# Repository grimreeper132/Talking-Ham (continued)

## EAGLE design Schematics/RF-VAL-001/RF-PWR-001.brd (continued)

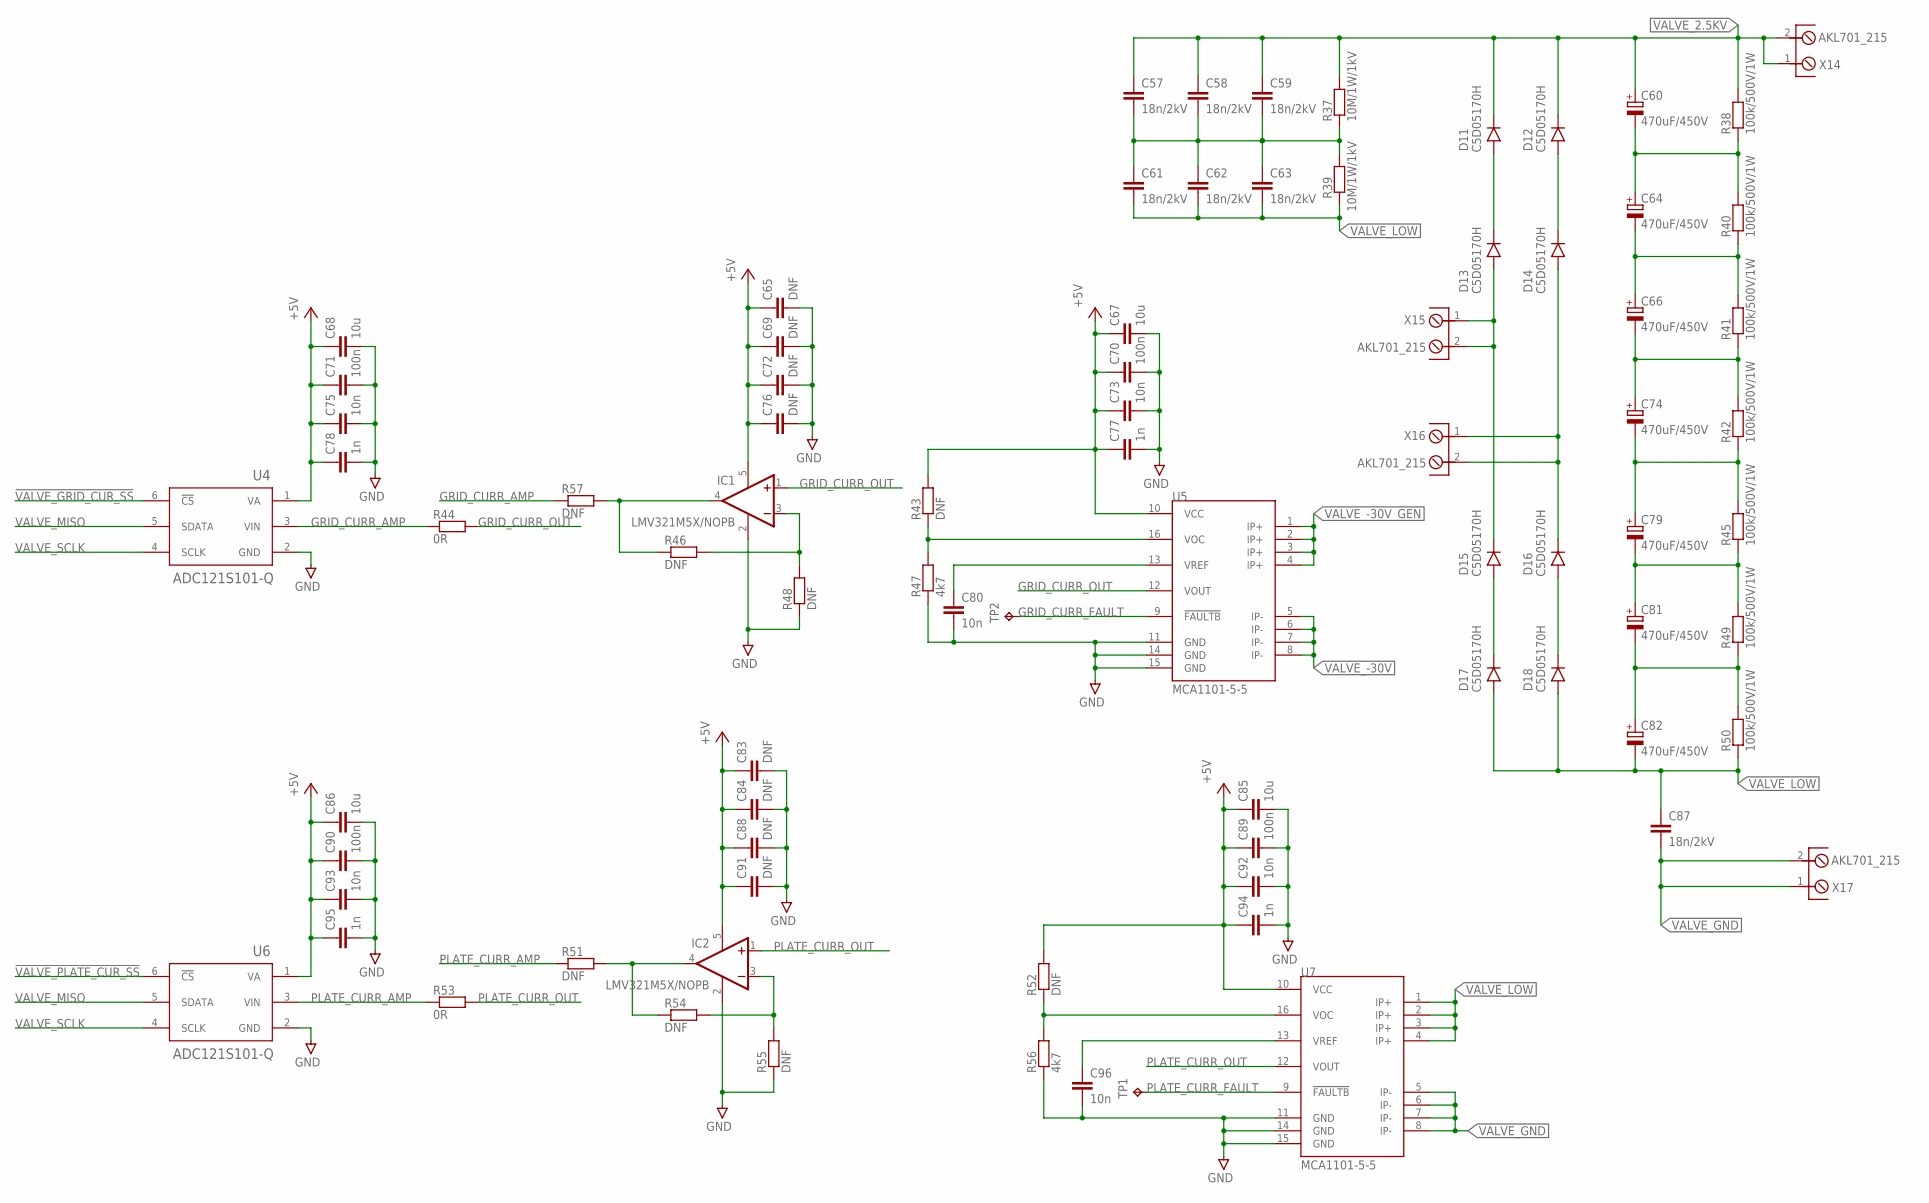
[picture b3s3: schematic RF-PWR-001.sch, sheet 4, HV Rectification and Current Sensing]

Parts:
C57, C58, C59, C61, C62, C63, C87: 18n/2kV; C050-075X075
C60, C64, C66, C74, C79, C81, C82: 470uF/450V; STYLE_D(35MM)
C65, C83: DNF; C0805
C67, C68, C85, C86: 10u; C0805
C69, C72, C76, C84, C88, C91: DNF; C0603
C70, C71, C89, C90: 100n; C0603
C73, C75, C80, C92, C93, C96: 10n; C0603
C77, C78, C94, C95: 1n; C0603
D11, D12, D13, D14, D15, D16, D17, D18: C5D05170H; TO-247-2
IC1, IC2: LMV321M5X/NOPB; SOT23-5
R37, R39: 10M/1W/1kV; R2512
R38, R40, R41, R42, R45, R49, R50: 100k/500V/1W; R2512
R43, R46, R48, R51, R52, R54, R55, R57: DNF; R0603
R44, R53: 0R; R0603
R47, R56: 4k7; R0603
TP1, TP2: TPTP16R; TP16R
U4, U6: ADC121S101-Q; SOT23-6
U5, U7: MCA1101-5-5; SOIC_16
X14, X15, X16, X17: AKL701_215; AKL701_2_15

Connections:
!VALVE_GRID_CUR_SS: U4.6 (!CS); also elsewhere on the board
!VALVE_PLATE_CUR_SS: U6.6 (!CS); also elsewhere on the board
+5V: C65.1, C67.1, C68.1, C69.1, C70.1, C71.1, C72.1, C73.1, C75.1, C76.1, C77.1, C78.1, C83.1, C84.1, C85.1, C86.1, C88.1, C89.1, C90.1, C91.1, C92.1, C93.1, C94.1, C95.1, IC1.5 (V+), IC2.5 (V+), R43.2, R52.2, U4.1 (VA), U5.10 (VCC), U6.1 (VA), U7.10 (VCC); also elsewhere on the board
GND: C65.2, C67.2, C68.2, C69.2, C70.2, C71.2, C72.2, C73.2, C75.2, C76.2, C77.2, C78.2, C80.2, C83.2, C84.2, C85.2, C86.2, C88.2, C89.2, C90.2, C91.2, C92.2, C93.2, C94.2, C95.2, C96.2, IC1.2 (V-), IC2.2 (V-), R47.1, R48.1, R55.1, R56.1, U4.2 (GND), U5.11 (GND), U5.14 (GND), U5.15 (GND), U6.2 (GND), U7.11 (GND), U7.14 (GND), U7.15 (GND); also elsewhere on the board
GRID_CURR_AMP: R44.1, R57.1, U4.3 (VIN)
GRID_CURR_FAULT: TP2.TP, U5.9 (!FAULTB)
GRID_CURR_OUT: IC1.1 (+IN), R44.2, U5.12 (VOUT)
unnamed: IC1.4 (OUT), R46.1, R57.2
unnamed: IC2.4 (OUT), R51.2, R54.1
unnamed: C81.-VE (-), C82.+VE (+), R49.1, R50.2
unnamed: D11.3 (ANODE), D13.1 (CATHODE)
unnamed: D15.3 (ANODE), D17.1 (CATHODE)
unnamed: D12.3 (ANODE), D14.1 (CATHODE)
unnamed: D16.3 (ANODE), D18.1 (CATHODE)
unnamed: C79.-VE (-), C81.+VE (+), R45.1, R49.2
unnamed: C66.-VE (-), C74.+VE (+), R41.1, R42.2
unnamed: C64.-VE (-), C66.+VE (+), R40.1, R41.2
unnamed: C60.-VE (-), C64.+VE (+), R38.1, R40.2
unnamed: C74.-VE (-), C79.+VE (+), R42.1, R45.2
unnamed: R52.1, R56.2, U7.16 (VOC)
unnamed: C96.1, U7.13 (VREF)
unnamed: C57.2, C58.2, C59.2, C61.1, C62.1, C63.1, R37.1, R39.2
unnamed: R43.1, R47.2, U5.16 (VOC)
unnamed: IC2.3 (-IN), R54.2, R55.2
unnamed: C80.1, U5.13 (VREF)
unnamed: IC1.3 (-IN), R46.2, R48.2
PLATE_CURR_AMP: R51.1, R53.1, U6.3 (VIN)
PLATE_CURR_FAULT: TP1.TP, U7.9 (!FAULTB)
PLATE_CURR_OUT: IC2.1 (+IN), R53.2, U7.12 (VOUT)
VALVE_2.5KV: C57.1, C58.1, C59.1, C60.+VE (+), D11.1 (CATHODE), D12.1 (CATHODE), R37.2, R38.2, X14.1, X14.2; also elsewhere on the board
VALVE_-30V: U5.5 (IP-), U5.6 (IP-), U5.7 (IP-), U5.8 (IP-); also elsewhere on the board
VALVE_-30V_GEN: U5.1 (IP+), U5.2 (IP+), U5.3 (IP+), U5.4 (IP+); also elsewhere on the board
VALVE_GND: C87.2, U7.5 (IP-), U7.6 (IP-), U7.7 (IP-), U7.8 (IP-), X17.1, X17.2; also elsewhere on the board
VALVE_LOW: C61.2, C62.2, C63.2, C82.-VE (-), C87.1, D17.3 (ANODE), D18.3 (ANODE), R39.1, R50.1, U7.1 (IP+), U7.2 (IP+), U7.3 (IP+), U7.4 (IP+)
VALVE_MISO: U4.5 (SDATA), U6.5 (SDATA); also elsewhere on the board
VALVE_PWR_+VE: D13.3 (ANODE), D15.1 (CATHODE), X15.1, X15.2
VALVE_PWR_-VE: D14.3 (ANODE), D16.1 (CATHODE), X16.1, X16.2
VALVE_SCLK: U4.4 (SCLK), U6.4 (SCLK); also elsewhere on the board

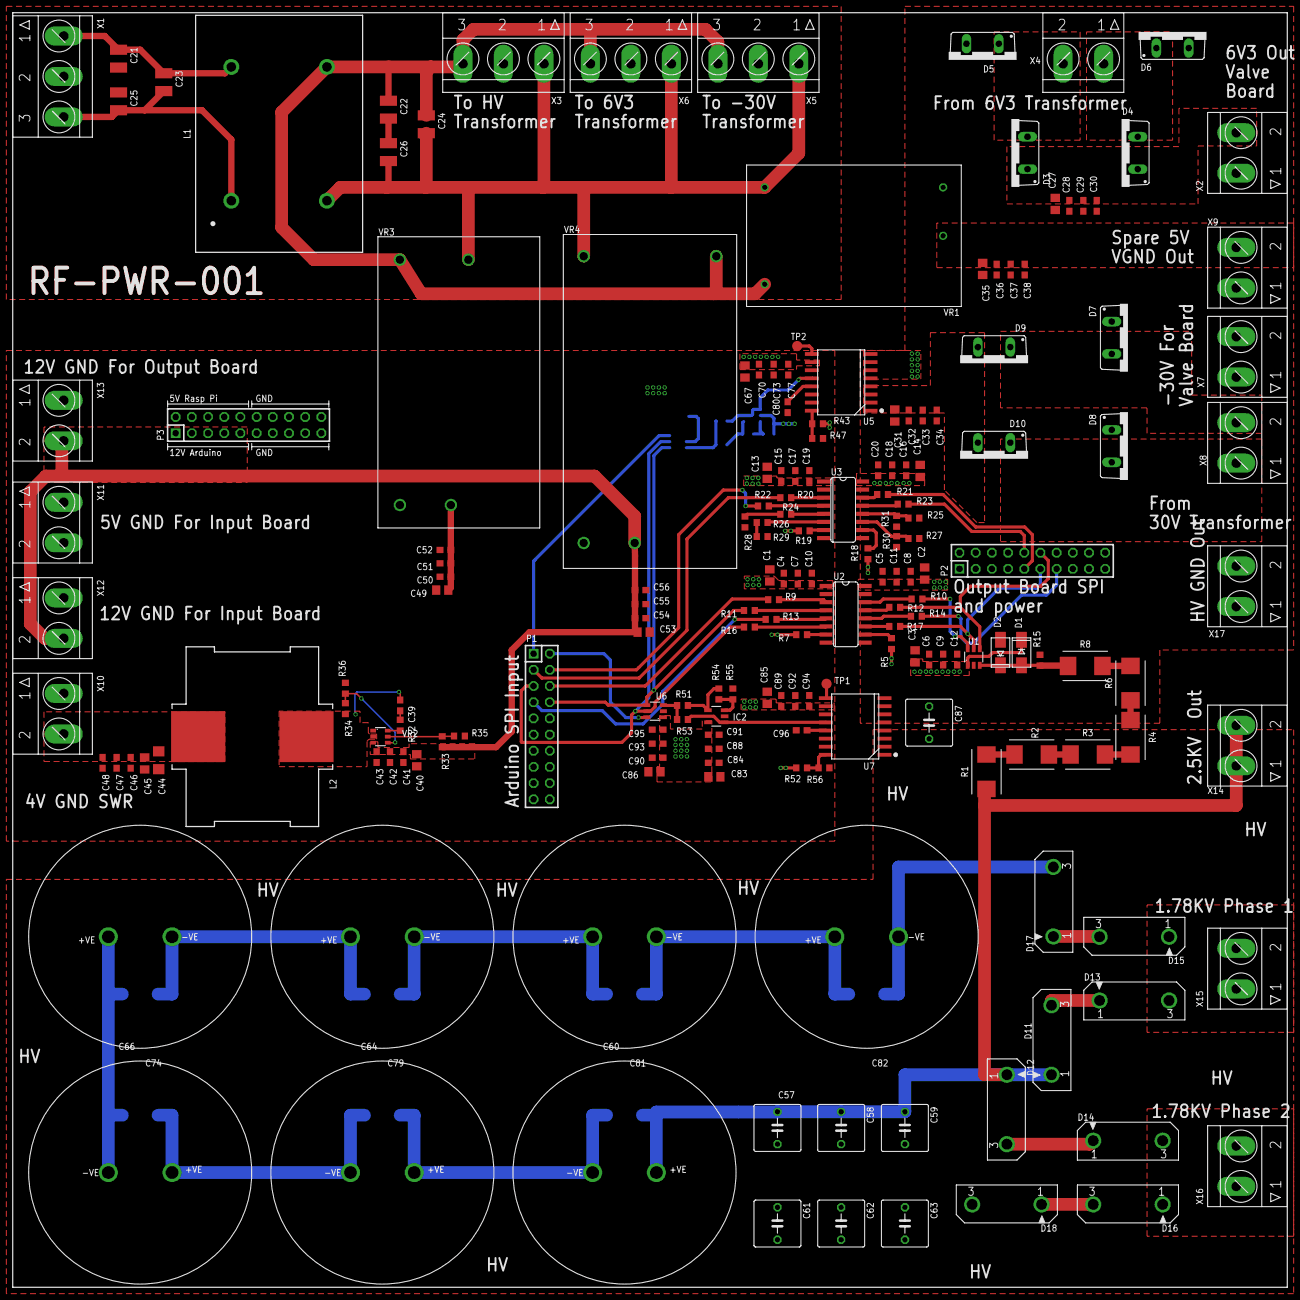
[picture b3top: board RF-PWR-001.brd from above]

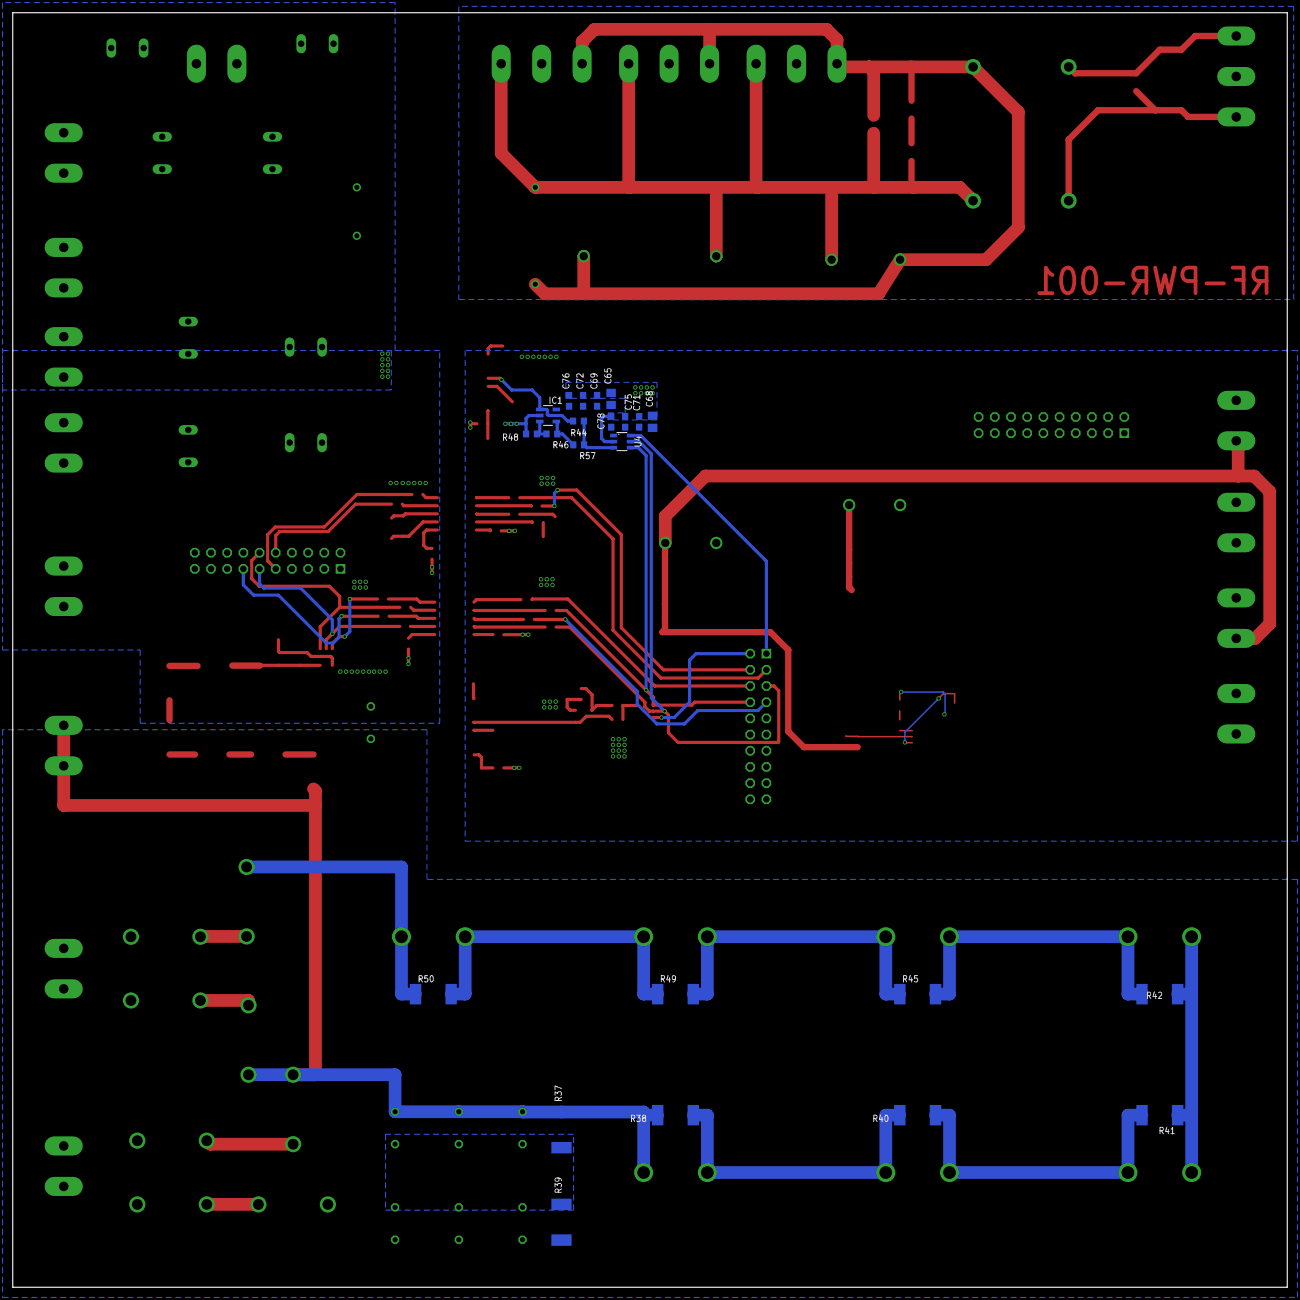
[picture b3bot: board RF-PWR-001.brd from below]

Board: 2 copper layers, 200.0 x 200.0 mm, 208 parts (23 on the bottom side), 94 nets.

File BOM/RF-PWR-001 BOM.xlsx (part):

|  |  | Board ID |  |  | Engineer |  |  | Project |  |  | Job NO.
 |  |  | Revision | 1 |  | Approval |  |  | Customer |  |  | Boards Required | 1
 | (don't touch)
 | Component Number | Type Colour | Schematic Ref | Quantity | Spare Parts | Description | Footprint | Value | Tolerance | Manufacturer | Manufacturer Part Number | Preferred Supplier | Order-code | Alternate Supplier | Alt Order-Code | Unit/Reel Price | Packaging | Reel QTY | Stock | Price per board | Total Price (all boards) | Order Quantity | Order Price
 | 0 | 1 | C1, C2, C3, C13, C14, C27, C30, C31, C34, C35, C49, C52, C53, C56, C67, C68, C8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 | 18 |  | X5R Ceramic Capacitor | C0805 | 10u/25V |  | Samsung Electro-Mechanics | CL21A106KAYNNNE | Mouser | 187-CL21A106KAYNNNE |  |  | 0.13700000000000001 | Cut Tape | 1000 |  | 2.4660000000000002 | 2.4660000000000002 | 18 | 2.4660000000000002
 | 1 | 1 | C10, C11, C12, C19, C20, C38, C77, C78, C94, C95 | 10 |  | C0G Ceramic Capacitor | C0603 | 1n/100V | 0.05 | Wurth Elektronik | 885012006085 | Mouser | 710-885012006085 |  |  | 7.6999999999999999E-2 | Cut Tape | 1000 |  | 0.77 | 0.77 | 10 | 0.77
 | 2 | 1 | C21, C22, C23, C24, C25, C26 | 6 |  | X7T Ceramic Capacitor | C1210 | 220/450V | 0.1 | TDK | CGA6M4X7T2W224K200AA | Mouser | 810-CGA6M4X7T2W224K |  |  | 0.60199999999999998 | Cut Tape | 1000 |  | 3.6120000000000001 | 3.6120000000000001 | 6 | 3.6120000000000001
 | 3 | 1 | C4, C5, C6, C15, C16, C28, C32, C36, C50, C54. C70, C71, C89, C90 | 13 |  | X7R Ceramic Capacitor | C0603 | 100n/100V | 0.1 | Samsung Electro-Mechanics | CL10B104KC8NNNC | Mouser | 187-CL10B104KC8NNNC |  |  | 7.6999999999999999E-2 | Cut Tape | 1000 |  | 1.0009999999999999 | 1.0009999999999999 | 13 | 1.0009999999999999
 | 4 | 1 | C7, C8, C9, C17, C18, C29, C33, C37, C51, C55, C73, C75, C80, C92, C93, C96 | 16 |  | X7R Ceramic Capacitor | C0603 | 10n/100V | 0.1 | KEMET | C0603C103K1RACTU | Mouser | 80-C0603C103K1R |  |  | 7.6999999999999999E-2 | Cut Tape | 1000 |  | 1.232 | 1.232 | 16 | 1.232
 | 5 | 1 | C57, C58, C59, C61, C62, C63, C87 | 7 |  | Ceramic Capacitor | C050-075X075 | 18n/2kV | 0.1 | KEMET | C330C183KGR5TA | Mouser | 80-C330C183KGR |  |  | 0.77 | Cut Tape | 1000 |  | 5.3900000000000006 | 5.3900000000000006 | 7 | 5.3900000000000006
 | 6 | 1 | C60, C64, C66, C74, C79, C81, C82 | 7 |  | Aluminium Capacitor | Style D | 330u/400V | 0.2 | Multicomp Pro | MCKLZ400M331O40Y | Farnell | CA08626 |  |  | 2.04 | Cut Tape | 1000 |  | 14.280000000000001 | 14.280000000000001 | 7 | 14.280000000000001
 | 7 | 2 | R1, R2, R3, R4, R6, R8 | 6 |  | Thick Film Resistor | SMF2 | 560k/2W | 0.05 | TE Connectivity/CGS | SMF2560KJT | Mouser | 279-SMF2560KJT |  |  | 0.45 | Cut Tape | 1000 |  | 2.7 | 2.7 | 6 | 2.7
 | 8 | 2 | R15 | 1 |  | Thick Film Resistor | R0603 | 3k3 | 0.01 | Vishay / Dale | CRCW06033K30FKEAC | Mouser | 71-CRCW06033K30FKEAC |  |  | 7.6999999999999999E-2 | Cut Tape | 1000 |  | 7.6999999999999999E-2 | 7.6999999999999999E-2 | 1 | 7.6999999999999999E-2
 | 9 | 2 | R37, R39 | 2 |  | Thick Film Resistor | R2512 | 10M/1W | 0.05 | Bourns | CHV2512-JW-106ELF | Mouser | CHV2512-JW-106ELF |  |  | 0.435 | Cut Tape | 1000 |  | 0.87 | 0.87 | 2 | 0.87
 | 10 | 2 | R38, R40, R41, R42, R45, R49, R50 | 7 |  | Thick Film Resistor | R2512 | 100K/1W | 0.05 | Vishay / Dale | CRCW2512100KJNEG | Mouser | 71-CRCW2512J-100K-E3 |  |  | 0.28199999999999997 | Cut Tape | 1000 |  | 1.9739999999999998 | 1.9739999999999998 | 7 | 1.9739999999999998
 | 11 | 2 | R44, R53 | 2 |  | Thick Film Resistor | R0603 | 0R |  | Vishay / Dale | CRCW06030000Z0EBC | Mouser | 71-CRCW06030000Z0EBC |  |  | 7.6999999999999999E-2 | Cut Tape | 1000 |  | 0.154 | 0.154 | 2 | 0.154
 | 12 | 2 | R5, R7, R18, R19, R28, R29, R30, R31, R47, R56 | 10 |  | Thick Film Resistor | R0603 | 4k7 | 0.05 | Vishay / Dale | CRCW06034K70JNEAC | Mouser | 71-CRCW06034K70JNEAC |  |  | 7.6999999999999999E-2 | Cut Tape | 1000 |  | 0.77 | 0.77 | 10 | 0.77
 | 13 | 2 | R9, R10, R11, R12, R13, R14, R16, R17, R20, R21, R22, R23, R24, R26 | 14 |  | Thick Film Resistor | R0603 | 100R | 0.01 | Vishay/Dale | CRCW0603100RFKEAC | Mouser | 71-CRCW0603100RFKEAC |  |  | 7.6999999999999999E-2 | Cut Tape | 1000 |  | 1.0780000000000001 | 1.0780000000000001 | 14 | 1.0780000000000001
 | 14 | 3 | L1 | 1 |  | Common Mode Choke | Custom | 3.9mH/6A |  | Wurth Elektronik | 744866392 | Mouser | 710-744866392 |  |  | 3.22 | Cut Tape | 1000 |  | 3.22 | 3.22 | 1 | 3.22
 | 15 | 3 | T1 | 1 |  | Power Transformer Inductor | External | 230V-1.78KV |  | Hammond Manufacturing | 726A | Digi-Key | HM5177-ND | Mouser | 546-726A | 87.78 | Cut Tape | 1000 |  | 87.78 | 87.78 | 1 | 87.78
 | 16 | 3 | T2 | 1 |  | LV Transformer Inductor | External | 230V-6V |  |  | 6-0-6 Vac Type 8A Secondary | Ebay | link |  |  | 14.91 | Cut Tape | 1000 |  | 14.91 | 14.91 | 1 | 14.91
 | 17 | 3 | T3 | 1 |  | LV Transformer Inductor | External | 230V-30V |  |  | 30-0-30 Vac Type 2A Secondary | Ebay | link |  |  | 17.3 | Cut Tape | 1000 |  | 17.3 | 17.3 | 1 | 17.3
 | 18 | 4 | D1, D2 | 2 |  | Schottky Diode | SMA | 1A/VF0.48V |  | ROHM Semiconductor | RBR1L30ADDTE25 | Mouser | 755-RBR1L30ADDTE25 |  |  | 0.374 | Cut Tape | 1000 |  | 0.748 | 0.748 | 2 | 0.748
 | 19 | 4 | D11, D12, D13, D14, D15, D16, D17, D18 | 8 |  | Schottky Diode | TO-247-2 | 18A/VR1700V |  | Wolfspeed/Cree | C5D05170H | Digi-Key | C5D05170H-ND |  |  | 3.49 | Cut Tape | 1000 |  | 27.92 | 27.92 | 8 | 27.92
 | 20 | 4 | D3, D4, D5, D6, D7, D8, D9, D10 | 8 |  | Schottky Diode | TO-220-2 | 10A/VR100V |  | Vishay General Semiconductor | MBR10100-M3/4W | Mouser | 78-MBR10100-M34W |  |  | 0.877 | Cut Tape | 1000 |  | 7.016 | 7.016 | 8 | 7.016
 | 21 | 4 | HSD11, HSD12, HSD13, HSD14, HSD15, HSD16, HSD17, HSD18 | 8 |  | Heatsinks for Schottky Rectifier Diodes | Custom | 25.9C/W |  | Aavid | 577102B04000G | Mouser | 532-577102B04000G |  |  | 0.33600000000000002 | Cut Tape | 1000 |  | 2.6880000000000002 | 2.6880000000000002 | 8 | 2.6880000000000002
 | 22 | 7 | IC1, IC2 | 2 |  | Op Amp | SOT 23-5 |  |  | STMicroelectronics | LMV321LILT | Mouser | 511-LMV321LILT |  |  | 0.30499999999999999 | Cut Tape | 1000 |  | 0.61 | 0.61 | 2 | 0.61
 | 23 | 7 | U1, U4, U6 | 3 |  | Analogue to Digital Convertor | SOT-23-6 | 12 bit |  | Texas Instruments | ADC121S101QIMF/NOPB | Mouser | 595-DC121S101QIMFNPB |  |  | 4.0599999999999996 | Cut Tape | 1000 |  | 12.18 | 12.18 | 3 | 12.18
 | 24 | 7 | U2, U3 | 2 |  | 4 Way Isolators | SOIC-16 | 4 Channel 3F/1B |  | Silicon Labs | SI8641AB-B-IS1 | Mouser | 634-SI8641AB-B-IS1 |  |  | 1.35 | Cut Tape | 1000 |  | 2.7 | 2.7 | 2 | 2.7
 | 25 | 7 | U5, U7 | 2 |  | Current Sensor | SOIC-16 | 5A |  | ACEINNA | MCA1101-5-5 | Mouser | 438-MCA1101-5-5 |  |  | 3.29 | Cut Tape | 1000 |  | 6.58 | 6.58 | 2 | 6.58
 | 26 | 7 | VR1 | 1 |  | AC/DC Converter | IRM-02 | 5V/2W |  | Mean Well | IRM-02-5 | Digi-Key | 1866-3009-ND |  |  | 4.42 | Cut Tape | 1000 |  | 4.42 | 4.42 | 1 | 4.42
 | 27 | 7 | VR3 | 1 |  | AC/DC Converter | IRM-05 | 5V/5W |  | Mean Well | IRM-05-5 | Digi-Key | 1866-3027-ND |  |  | 5.94 | Cut Tape | 1000 |  | 5.94 | 5.94 | 1 | 5.94
 | 28 | 7 | VR4 | 1 |  | AC/DC Converter | IRM-15 | 12V/20W |  | Mean Well | IRM-20-12 | Digi-Key | 1866-3038-ND |  |  | 7.79 | Cut Tape | 1000 |  | 7.79 | 7.79 | 1 | 7.79
 | 29 | 8 | X2, X4, X7, X8, X9, X10, X11, X12, X13, X14, X15, X16, X17 | 13 |  | Terminal Block | 6.35mm 2 pos | 2 pos |  | Phoenix Contact | 1714955 | Mouser | 651-1714955 | Digi-Key | 277-1269-ND | 0.96299999999999997 | Cut Tape | 1000 |  | 12.519 | 12.519 | 13 | 12.519
 | 30 | 8 | X1, X3, X5, X6 | 4 |  | Terminal Block | 6.35mm 3 pos | 3 pins |  | Phoenix Contact | 1714968 | Mouser | 651-1714968 | Digi-Key | 277-1270-ND | 1.4 | Cut Tape | 1000 |  | 5.6 | 5.6 | 4 | 5.6
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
